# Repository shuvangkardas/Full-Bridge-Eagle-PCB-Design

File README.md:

# H-Bridge PCB
<!-- Badges -->
<!-- [![Build Status][build-shield]][build-url] -->
[![GitHub release][release-shield]][release-url]
[![GitHub commits][commits-shield]][commits-url]
[![MIT License][license-shield]][license-url]

[![Twitter][twitter-shield]][twitter-url]
[![LinkedIn][linkedin-shield]][linkedin-url]
[![Follow GitHub][github-shield]][github-url]
[![YouTube][youtube-shield]][youtube-url]

# H-bridge and drivers Eagle PCB design 

<sup> Please download the latest stable release from [here][download-latest]. Please report any bugs in [issues][report-bug].</sup>

This repository is the official PCB of my paper [Design and Hardware Implementation Considerations of Modified Multilevel Cascaded H-Bridge Inverter for Photovoltaic System](https://www.researchgate.net/publication/329921455_Design_and_Hardware_Implementation_Considerations_of_Modified_Multilevel_Cascaded_H-Bridge_Inverter_for_Photovoltaic_System) we published in 2019.

**Special features of the design are**
- Completely modular design. The H-bridge and driver circuits are completely modular. 
- I have included 2 types of driver circuit. The driver circuits are similar design so that these can be connected and disconected with the H-bridge in easy ways. 

## Schematic and PCB
Here is the schematic and PCB of H-bridge circuit

I have included few types of driver circuit with the project. The driver circuits are modular design on the top of the H-bridge. Here is the IR2111 driver circuit. This circuit is optically isolated. 

# How to cite the paper
If you use the driver circuits and PCB design for your research, please cite publication as follow:

- S. Shuvo, E. Hossain, T. Islam, A. Akib, S. Padmanaban and M. Z. R. Khan, "Design and Hardware Implementation Considerations of Modified Multilevel Cascaded H-Bridge Inverter for Photovoltaic System," in IEEE Access, vol. 7, pp. 16504-16524, 2019, doi: 10.1109/ACCESS.2019.2894757.

# Credits
- [Shuvangkar Chandra Das](https://www.linkedin.com/in/shuvangkar/) - Lead Researcher
- Abir Ahsan Akib
- Tanveerul Islam 
- Ziaur Rahman Khan - Project Supervisor
- Eklas Hossain - Project Supervisor

# License
MIT

<!-- Social Links -->
[twitter-shield]: https://img.shields.io/twitter/follow/shuvangkar_das?style=social&logo=twitter
[twitter-url]: https://twitter.com/intent/follow?screen_name=shuvangkar_das

[linkedin-shield]: https://img.shields.io/badge/-LinkedIn-black.svg?logo=linkedin&colorB=555
[linkedin-url]: https://linkedin.com/in/shuvangkar

[youtube-url]: https://www.youtube.com/channel/UCU6T54Uu5Mgd6NwYbnXaosA
[youtube-shield]: https://img.shields.io/youtube/channel/subscribers/UCU6T54Uu5Mgd6NwYbnXaosA?style=social

[github-shield]: https://img.shields.io/github/followers/shuvangkar?style=social
[github-url]: https://github.com/shuvangkar

[ResearchGate-url]:  https://www.researchgate.net/profile/Shuvangkar-Das
[Google Scholar-url]: https://scholar.google.com/citations?user=ebLUEXQAAAAJ

[build-url]: https://travis-ci.com/github/shuvangkar/SIM800L

[release-shield]: https://img.shields.io/github/release/shuvangkar/SIM800L.svg
[release-url]: https://github.com/shuvangkar/SIM800L

[commits-shield]: https://img.shields.io/github/commits-since/shuvangkar/SIM800L/v0.1.0
[commits-url]: https://img.shields.io/github/commits-since/shuvangkar/SIM800L/v0.1.0

[license-shield]: https://img.shields.io/github/license/shuvangkar/SIM800L
[license-url]: https://github.com/shuvangkar/SIM800L/blob/master/LICENSE.txt

<!-- Product Screenshot -->
[product-screenshot]: resources/screenshot1.png

<!-- Download links -->
[download-latest]:https://github.com/shuvangkar/SIM800L/releases/latest
[report-bug]: https://github.com/shuvangkar/SIM800L/issues/new

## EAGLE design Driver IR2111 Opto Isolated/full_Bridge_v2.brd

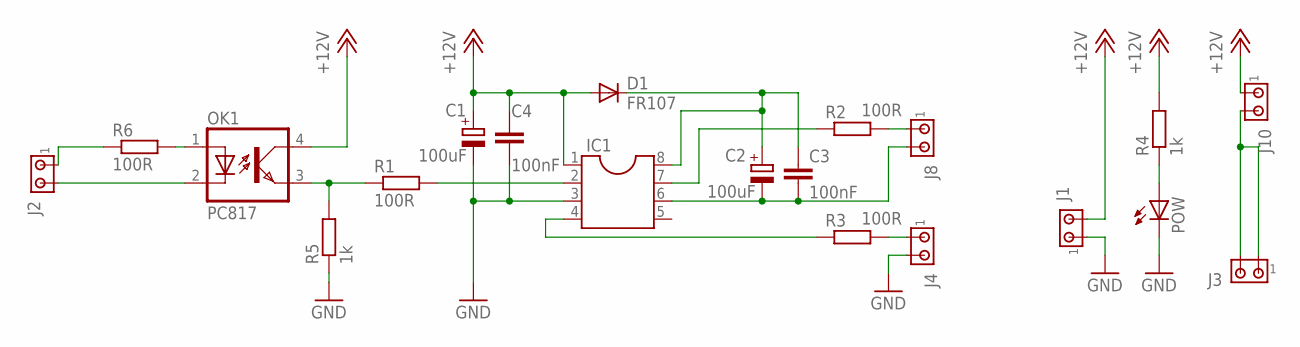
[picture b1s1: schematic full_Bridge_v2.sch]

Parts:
C1: 100uF; E2,5-6E
C2: 100uF; E2,5-7
C3, C4: 100nF; C050-024X044
D1: FR107; DO41-10
IC1: DIL8; DIL08
J1, J2, J3, J4, J8, J10: MTA02-100; 10X02MTA
OK1: PC817; DIL04
POW: LED3MM
R1, R2, R6: 100R; 0204/7
R3: 100R; 0207/12
R4, R5: 1k; 0204/7

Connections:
+12V: C1.+, C4.1, D1.A, IC1.1, J1.2, J10.1, OK1.4 (COL), R4.2
GND: C1.-, C4.2, IC1.3, J1.1, J4.2, POW.K (C), R5.1
unnamed: POW.A, R4.1
unnamed: J3.1, J3.2, J10.2
unnamed: OK1.3 (EMIT), R1.1, R5.2
unnamed: C2.-, C3.2, IC1.6, J8.2
unnamed: C2.+, C3.1, D1.C, IC1.8
unnamed: J2.2, OK1.2 (C)
unnamed: IC1.7, R2.1
unnamed: IC1.4, R3.1
unnamed: IC1.2, R1.2
unnamed: OK1.1 (A), R6.2
unnamed: J8.1, R2.2
unnamed: J4.1, R3.2
unnamed: J2.1, R6.1

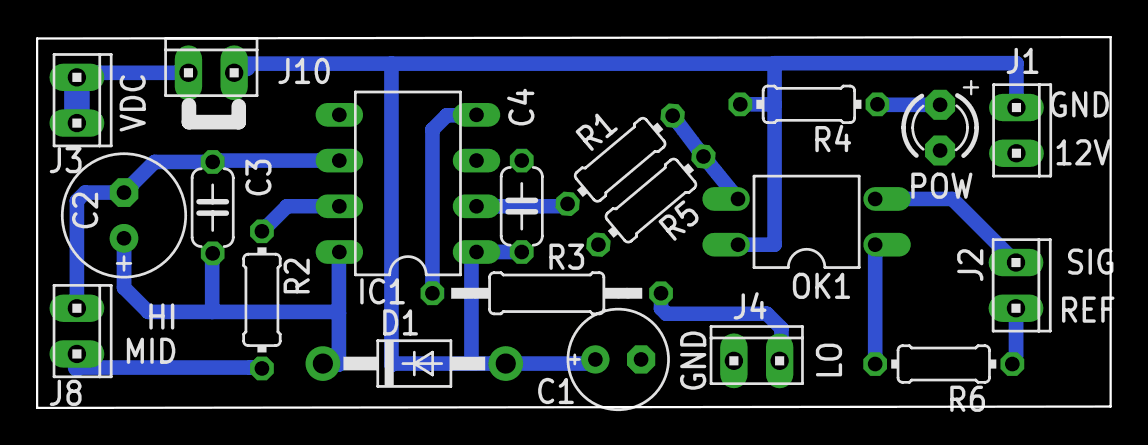
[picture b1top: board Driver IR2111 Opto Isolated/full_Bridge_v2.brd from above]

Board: 2 copper layers, 59.6 x 20.6 mm, 20 parts (0 on the bottom side), 15 nets.

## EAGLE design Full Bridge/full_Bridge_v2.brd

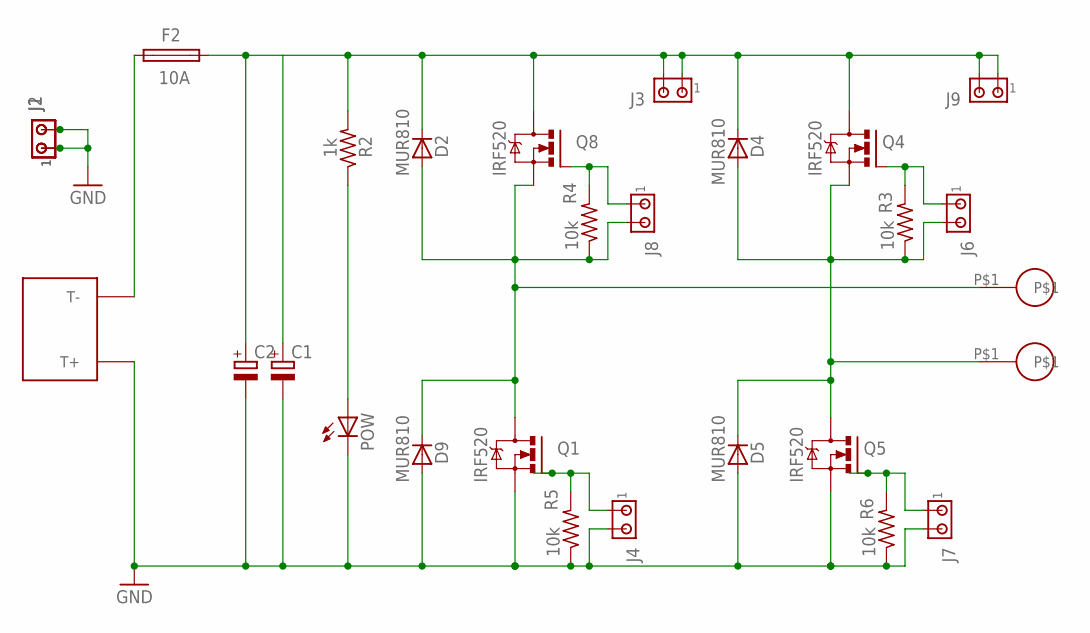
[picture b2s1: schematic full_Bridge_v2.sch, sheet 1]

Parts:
AC1, AC2: TERMINAL
C1, C2: CPOL-EUTT5D10; TT5D10
D2, D4, D5, D9: MUR810; TO220ACS
F2: 10A; SH22,5A
J1, J2, J3, J4, J6, J7, J8, J9: MTA02-100; 10X02MTA
POW: LED3MM
Q1, Q4, Q5, Q8: IRF520; TO220BV
R2: 1k; 0207/12
R3, R4, R5, R6: 10k; 0204/7
U$5: CONNECTOR_BIG

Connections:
A_MID: AC1.P$1, D2.A, D9.C, J8.2, Q1.D, Q8.S, R4.1
A_MID1: AC2.P$1, D4.A, D5.C, J6.2, Q4.S, Q5.D, R3.1
DC_BUS: C1.+, C2.+, D2.C, D4.C, F2.1, J3.1, J3.2, J9.1, J9.2, Q4.D, Q8.D, R2.2
GND: C1.-, C2.-, D5.A, D9.A, J1.1, J1.2, J2.1, J2.2, J4.2, J7.2, POW.K (C), Q1.S, Q5.S, R5.1, R6.1, U$5.P$1 (T+)
IN+: F2.2, U$5.P$2 (T-)
unnamed: POW.A, R2.1
unnamed: J6.1, Q4.G, R3.2
unnamed: J7.1, Q5.G, R6.2
unnamed: J4.1, Q1.G, R5.2
unnamed: J8.1, Q8.G, R4.2

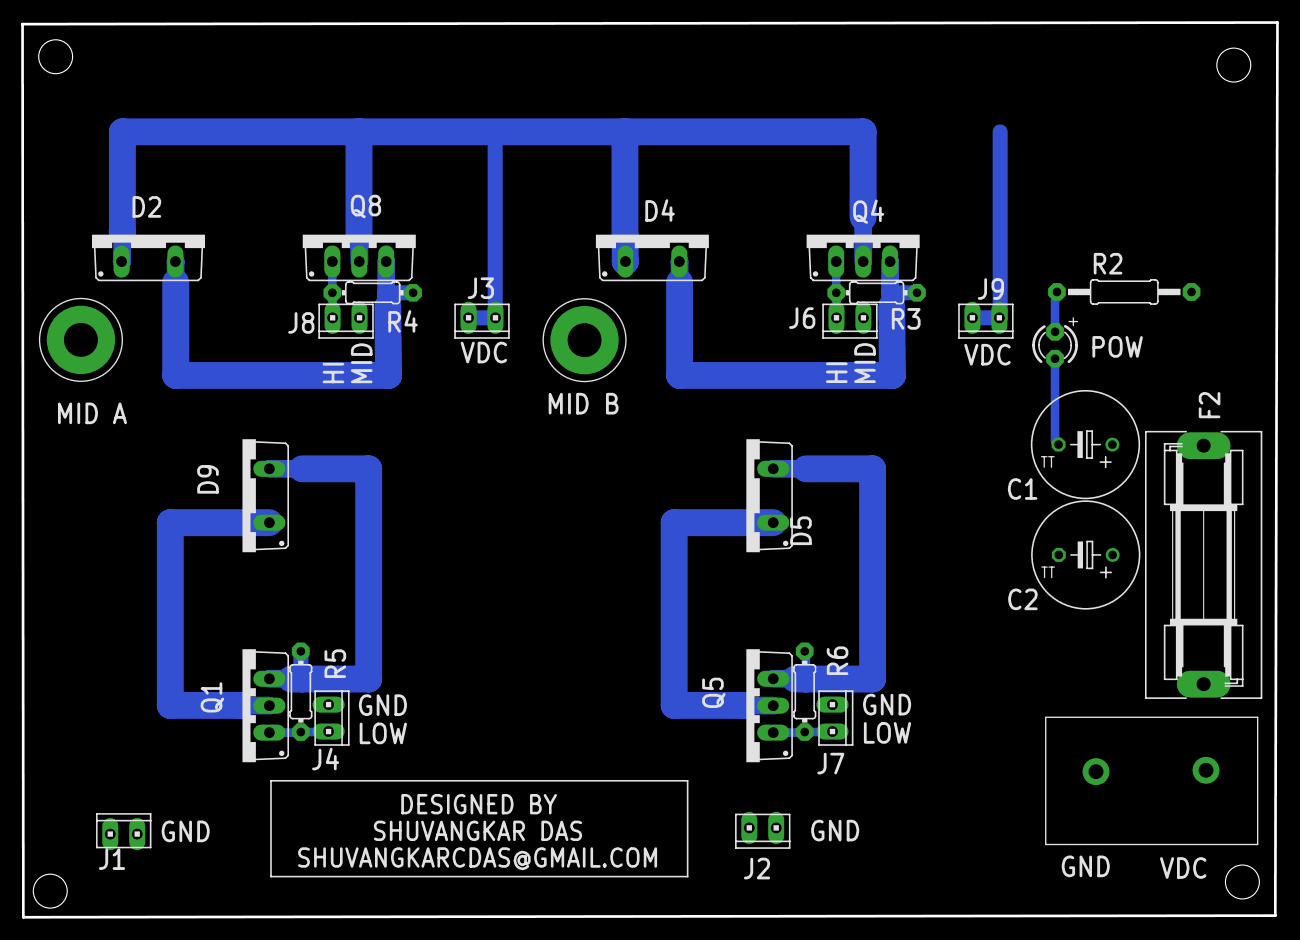
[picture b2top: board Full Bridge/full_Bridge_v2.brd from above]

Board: 2 copper layers, 118.4 x 84.4 mm, 28 parts (0 on the bottom side), 10 nets.

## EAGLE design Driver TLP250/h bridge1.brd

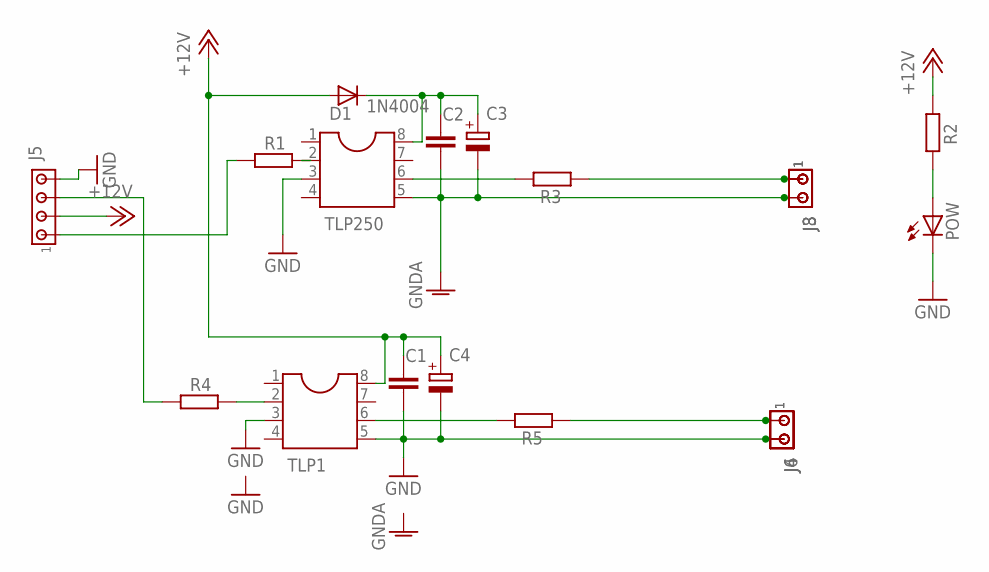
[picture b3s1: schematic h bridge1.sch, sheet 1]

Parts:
C1, C2: C-EU025-025X050; C025-025X050
C3, C4: CPOL-EUE2.5-6; E2,5-6
D1: 1N4004; DO41-10
J3, J4, J6, J8: MTA02-100; 10X02MTA
J5: MTA04-100; 10X04MTA
POW: LED3MM
R1, R2, R3, R4, R5: R-EU_0204/7; 0204/7
TLP1, TLP250: DIL8; DIL08

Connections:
+12V: C1.1, C4.+, D1.A, J5.2, R2.1, TLP1.8
GND: C1.2, C4.-, J4.2, J5.4, J6.2, POW.K (C), TLP1.3, TLP1.5, TLP250.3
GNDA: C2.2, C3.-, J3.2, J8.2, TLP250.5
unnamed: R1.2, TLP250.2
unnamed: J3.1, J8.1, R3.1
unnamed: C2.1, C3.+, D1.C, TLP250.8
unnamed: R3.2, TLP250.6
unnamed: J5.1, R1.1
unnamed: POW.A, R2.2
unnamed: R5.2, TLP1.6
unnamed: J4.1, J6.1, R5.1
unnamed: R4.2, TLP1.2
unnamed: J5.3, R4.1

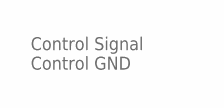
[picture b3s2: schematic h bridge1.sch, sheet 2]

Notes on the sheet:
Control Signal Control GND

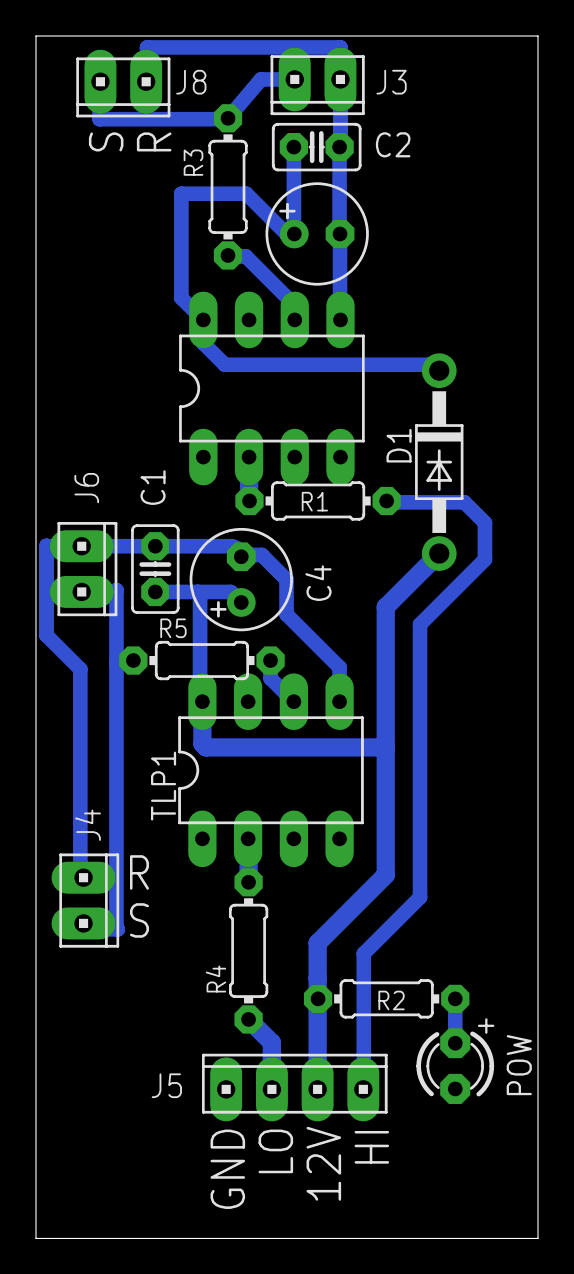
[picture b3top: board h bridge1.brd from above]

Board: 2 copper layers, 27.9 x 66.8 mm, 18 parts (0 on the bottom side), 13 nets.

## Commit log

2022-04-10 h-bridge components value updated
2022-04-17 IR2111 optical isolated driver updated
2022-04-17 description updated
